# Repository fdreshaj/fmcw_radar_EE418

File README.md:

# fmcw_radar_EE418
FMCW Radar Design at 26.5 - 40 GHz

Initial Systems Level Overview
Bistatic Design

Monostatic Design

Initial Parts Search Tx bistatic:

MCU 

STM32H730VBT6

Synthesizer 
	ADF4371 62.5MHz - 32 GHz
	Refer to datasheet for more info 
	3.3V, 5V, min 200mA
	Pout = -7dBm at 30 GHz

PA  
    MAAP-118260 18-26 GHz 28.5 dB,28.5 dBm, 24 QFN
    MAAP-011319 24-30 GHz 24 dB, 27 dBm PSAT 24 QFN

Dir Coupler 
    FPC07181 20GHz ~ 40GHz 20dB 0.3dB IL, 15 dB RL

ADC

    AD4080 20 Bit 40 MSPS Differential SAR 

LNA

	PMA3-24323LN+ 24-32 GHz, fluctuates around 14.5 to 15.1 dB
	Operating Vs 4.75-5.25

TX Mixer

	ADAR2001 In 2.5-10 GHz
	2.5V analog supply, 1.8 digital supply, 4x Freq 
	Differential

RX Mixer

	ADAR2004 RF In 10-40 GHz, LO In  2.4-10.1 GHz, IF Out  0-800 MHz
	2.5V analog supply, 1.8V digital, Gain Range 21-41 dB
	Differential

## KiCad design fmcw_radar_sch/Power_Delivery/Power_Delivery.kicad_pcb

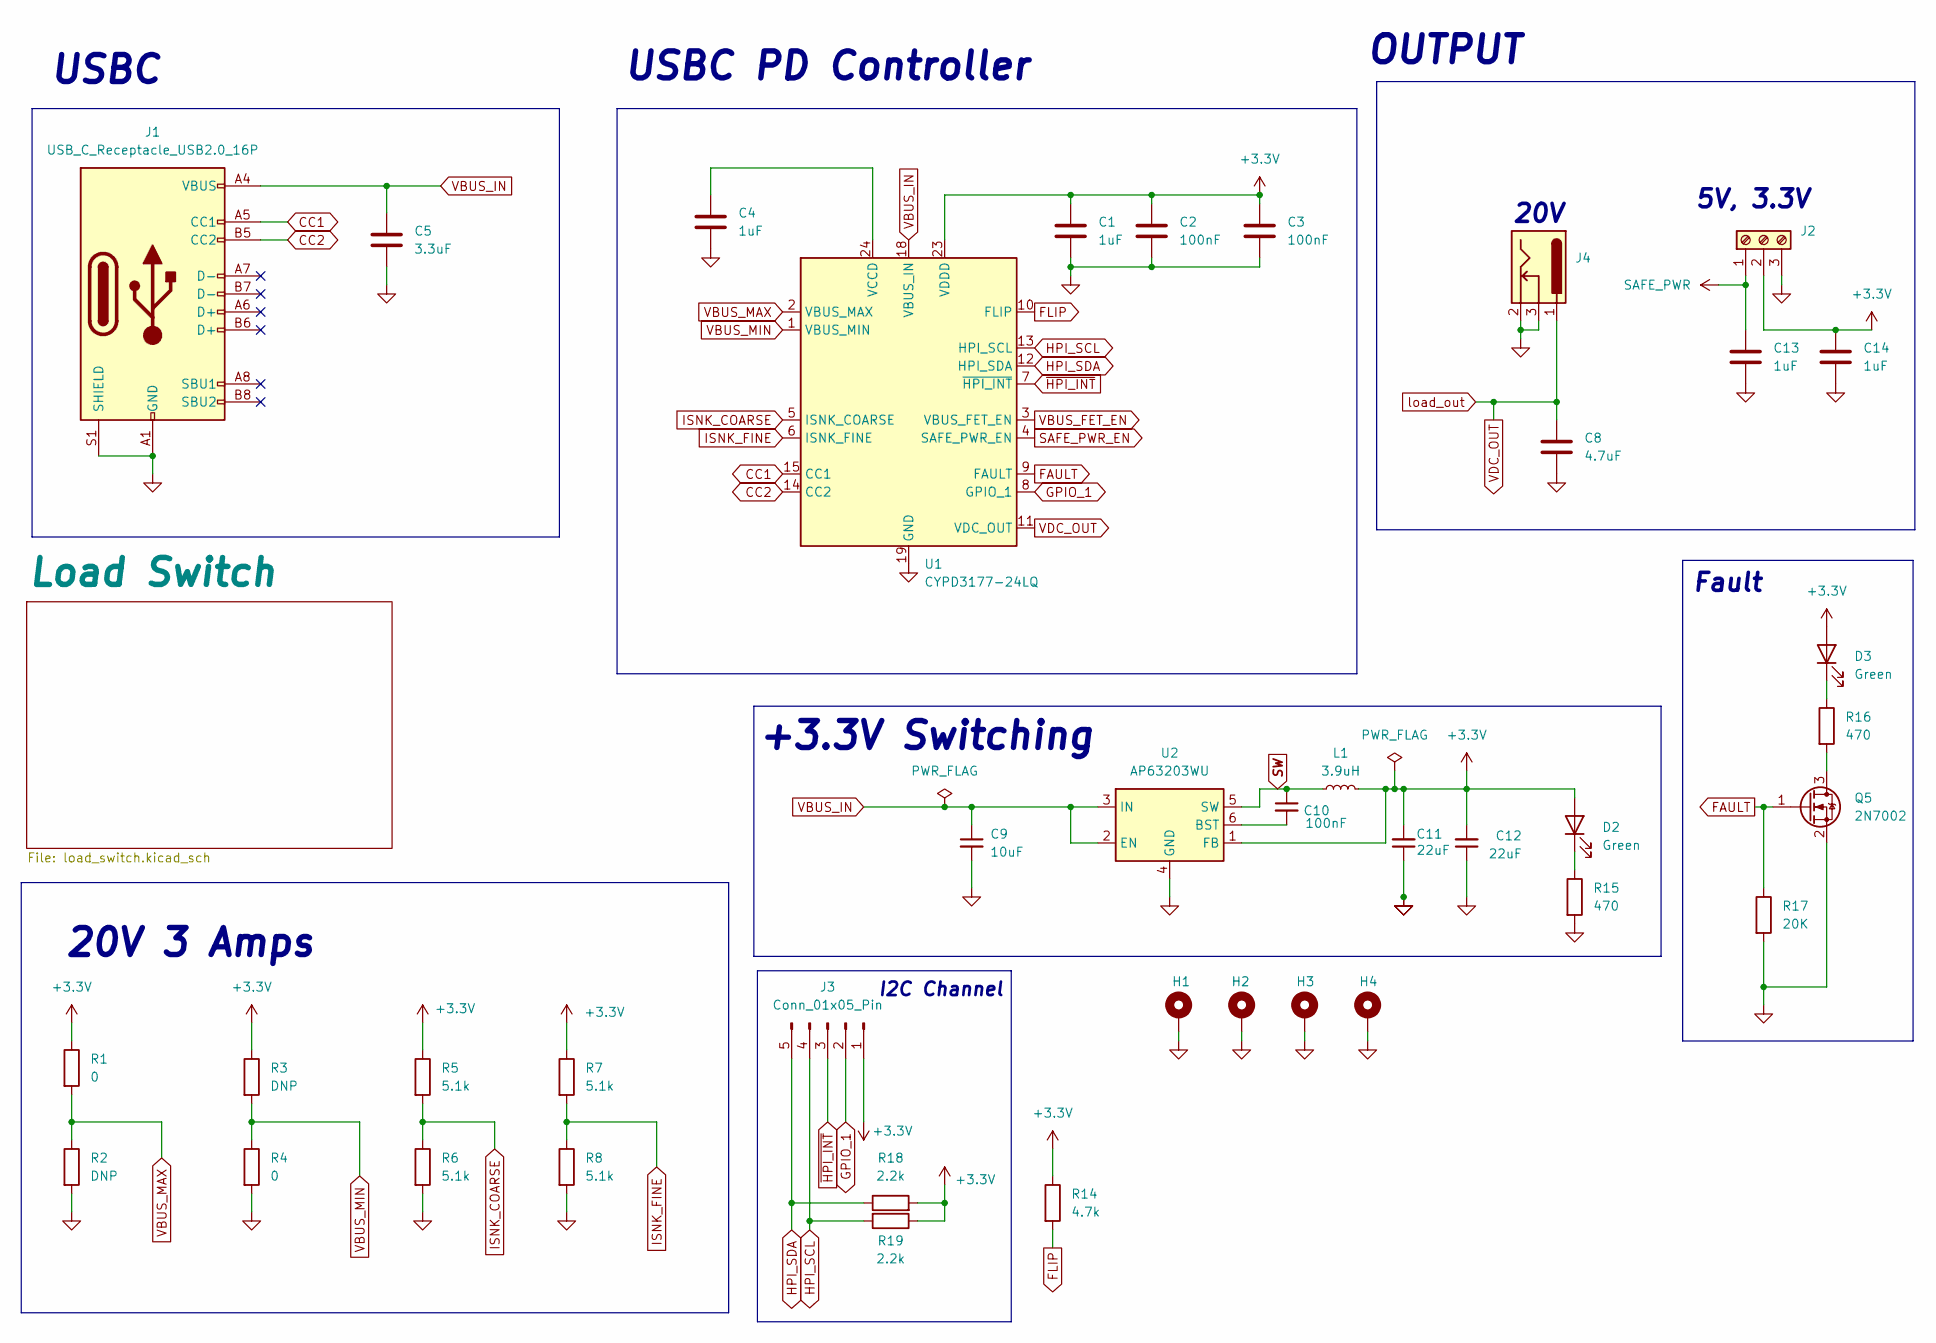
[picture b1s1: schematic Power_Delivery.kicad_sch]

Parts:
C1, C4, C13, C14: 1uF; C_0603_1608Metric
C2, C3, C10: 100nF; C_0603_1608Metric
C5: 3.3uF; C_0603_1608Metric
C8: 4.7uF; C_0603_1608Metric
C9: 10uF; C_0603_1608Metric
C11, C12: 22uF; C_1206_3216Metric
D2, D3: Green; LED_0603_1608Metric
H1, H2, H3, H4: MountingHole_Pad; MountingHole_2.5mm_Pad
J1: USB_C_Receptacle_USB2.0_16P; USB_C_Receptacle_G-Switch_GT-USB-7010ASV
J2: Screw_Terminal_01x03; TerminalBlock_Phoenix_MKDS-1,5-3-5.08_1x03_P5.08mm_Horizont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
J3: Conn_01x05_Pin; PinHeader_1x05_P2.54mm_Vertical
J4: Barrel_Jack_Switch; BarrelJack_GCT_DCJ200-10-A_Horizontal
L1: 3.9uH; L_Bourns_SDR0604
Q5: 2N7002; SOT-23
R1, R4: 0; R_0603_1608Metric
R2, R3: DNP; R_0603_1608Metric
R5, R6, R7, R8: 5.1k; R_0603_1608Metric
R14: 4.7k; R_0603_1608Metric
R15, R16: 470; R_0603_1608Metric
R17: 20K; R_0603_1608Metric
R18, R19: 2.2k; R_0603_1608Metric
U1: CYPD3177-24LQ; QFN-24-1EP_4x4mm_P0.5mm_EP2.75x2.75mm
U2: AP63203WU; TSOT-23-6

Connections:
+3.3V: C1.1, C2.1, C3.1, C11.2, C12.2, C14.2, D2.2 (A), D3.2 (A), J2.2, J3.1, L1.2, R1.1, R3.1, R5.1, R7.1, R14.1, R18.2, R19.1, U1.23 (VDDD), U2.1 (FB)
CC1: J1.A5 (CC1), U1.15 (CC1)
CC2: J1.B5 (CC2), U1.14 (CC2)
FAULT: Q5.1 (G), R17.1, U1.9 (FAULT)
FLIP: R14.2, U1.10 (FLIP)
GND: C1.2, C2.2, C3.2, C4.2, C5.2, C8.1, C9.2, C11.1, C12.1, C13.1, C14.1, H1.1, H2.1, H3.1, H4.1, J1.A1 (GND), J1.A12 (GND), J1.B1 (GND), J1.B12 (GND), J1.S1 (SHIELD), J2.3, J4.2, J4.3, Q5.2 (S), R2.2, R4.2, R6.2, R8.2, R15.2, R17.2, U1.19 (GND), U1.22 (GND), U1.25 (GND), U2.4 (GND)
GPIO_1: J3.2, U1.8 (GPIO_1)
HPI_SCL: J3.4, R19.2, U1.13 (HPI_SCL)
HPI_SDA: J3.5, R18.1, U1.12 (HPI_SDA)
ISNK_COARSE: R5.2, R6.1, U1.5 (ISNK_COARSE)
ISNK_FINE: R7.2, R8.1, U1.6 (ISNK_FINE)
unnamed: D2.1 (K), R15.1
unnamed: D3.1 (K), R16.1
unnamed: Q5.3 (D), R16.2
unnamed: C4.1, U1.24 (VCCD)
unnamed: C10.2, U2.6 (BST)
SAFE_PWR: C13.2, J2.1; also elsewhere on the board
SAFE_PWR_EN: U1.4 (SAFE_PWR_EN); also elsewhere on the board
SW: C10.1, L1.1, U2.5 (SW)
VBUS_FET_EN: U1.3 (VBUS_FET_EN); also elsewhere on the board
VBUS_IN: C5.1, C9.1, J1.A4 (VBUS), J1.A9 (VBUS), J1.B4 (VBUS), J1.B9 (VBUS), U1.18 (VBUS_IN), U2.2 (EN), U2.3 (IN); also elsewhere on the board
VBUS_MAX: R1.2, R2.1, U1.2 (VBUS_MAX)
VBUS_MIN: R3.2, R4.1, U1.1 (VBUS_MIN)
VDC_OUT: C8.2, J4.1, U1.11 (VDC_OUT); also elsewhere on the board
~HPI_INT: J3.3, U1.7 (~HPI_INT)

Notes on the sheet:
5V, 3.3V
USBC
20V
Fault
I2C Channel
OUTPUT
USBC PD Controller
20V 3 Amps
+3.3V Switching

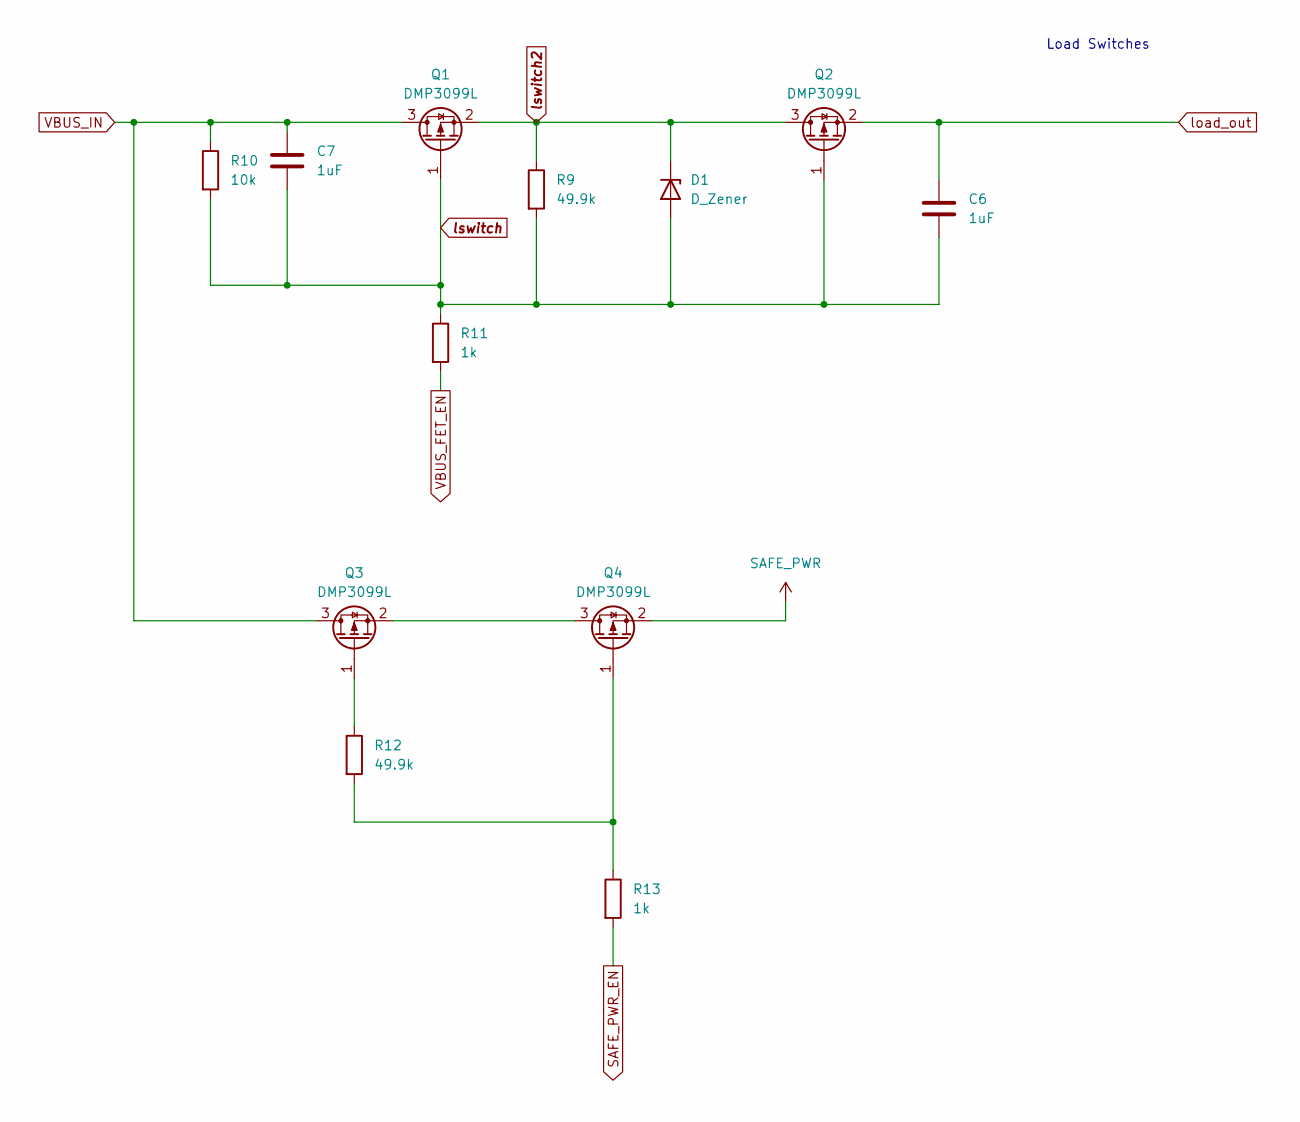
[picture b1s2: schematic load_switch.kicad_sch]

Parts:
C6, C7: 1uF; C_0603_1608Metric
D1: D_Zener; D_0603_1608Metric
Q1, Q2, Q3, Q4: DMP3099L; SOT-23
R9, R12: 49.9k; R_0603_1608Metric
R10: 10k; R_0603_1608Metric
R11, R13: 1k; R_0603_1608Metric

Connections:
unnamed: Q3.1 (G), R12.1
unnamed: Q3.2 (S), Q4.3 (D)
unnamed: Q4.1 (G), R12.2, R13.1
SAFE_PWR: Q4.2 (S); also elsewhere on the board
SAFE_PWR_EN: R13.2; also elsewhere on the board
VBUS_FET_EN: R11.2; also elsewhere on the board
VBUS_IN: C7.1, Q1.3 (D), Q3.3 (D), R10.1; also elsewhere on the board
VDC_OUT: C6.1, Q2.2 (S); also elsewhere on the board
lswitch: C6.2, C7.2, D1.2 (A), Q1.1 (G), Q2.1 (G), R9.2, R10.2, R11.1
lswitch2: D1.1 (K), Q1.2 (S), Q2.3 (D), R9.1

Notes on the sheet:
Load Switches

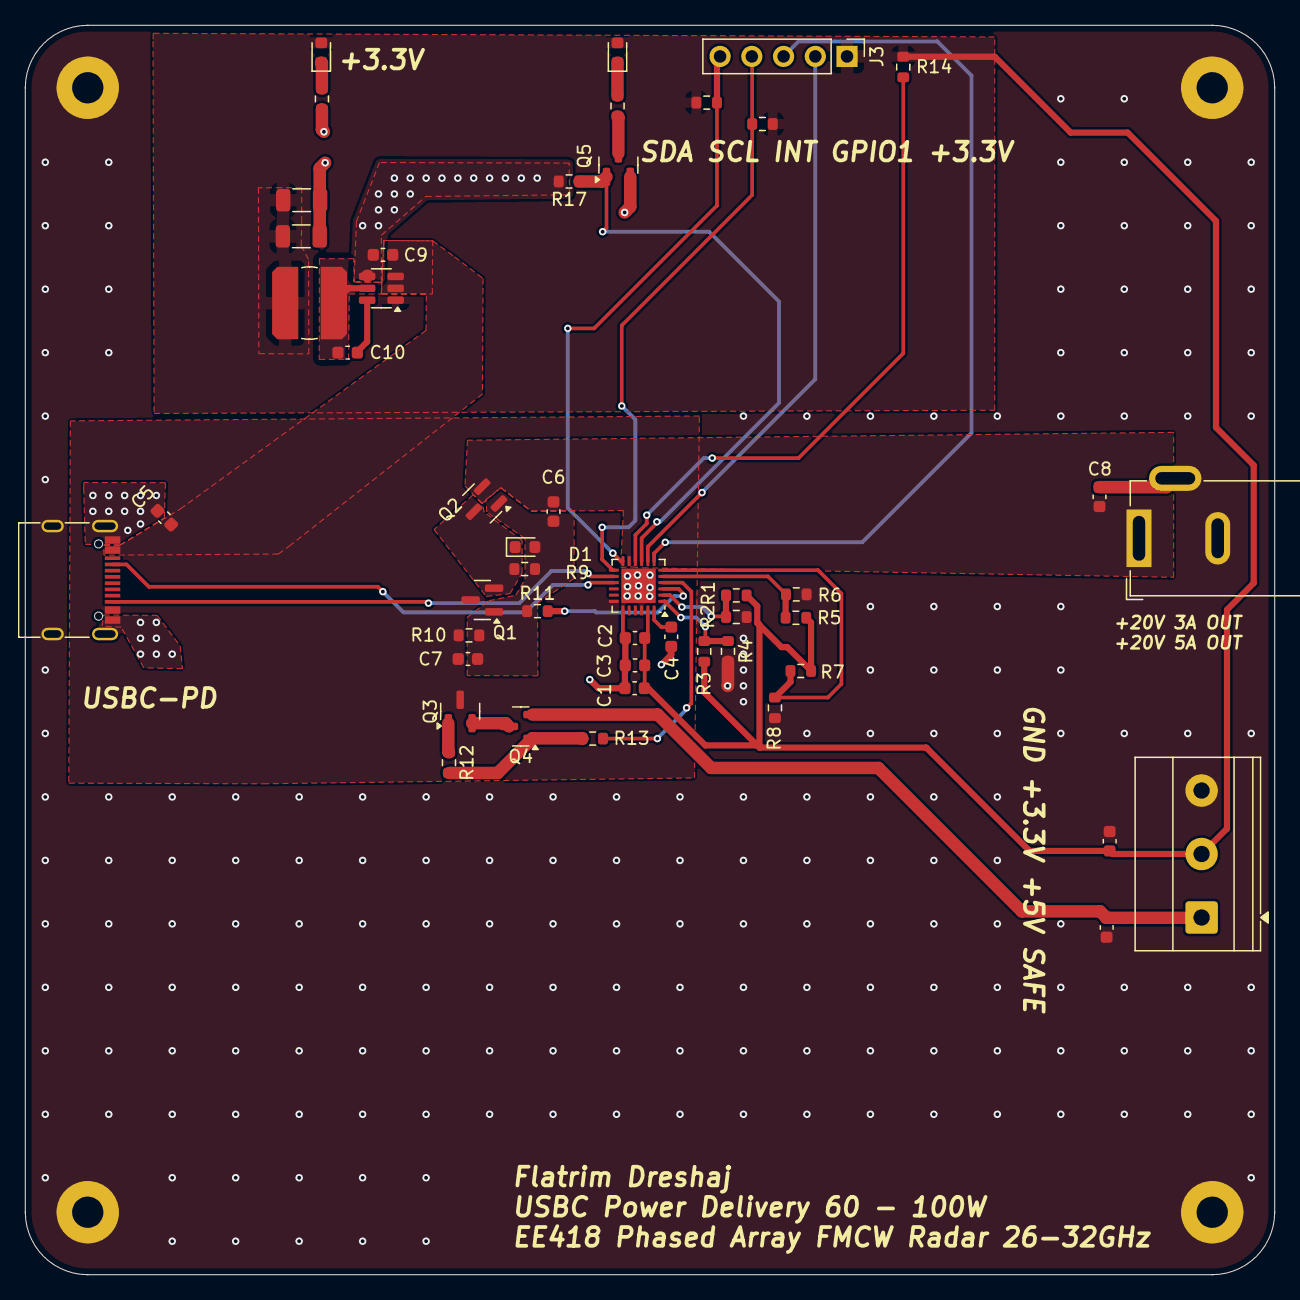
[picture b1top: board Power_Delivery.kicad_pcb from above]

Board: 2 copper layers, 100.0 x 100.0 mm, 52 parts (0 on the bottom side), 30 nets.

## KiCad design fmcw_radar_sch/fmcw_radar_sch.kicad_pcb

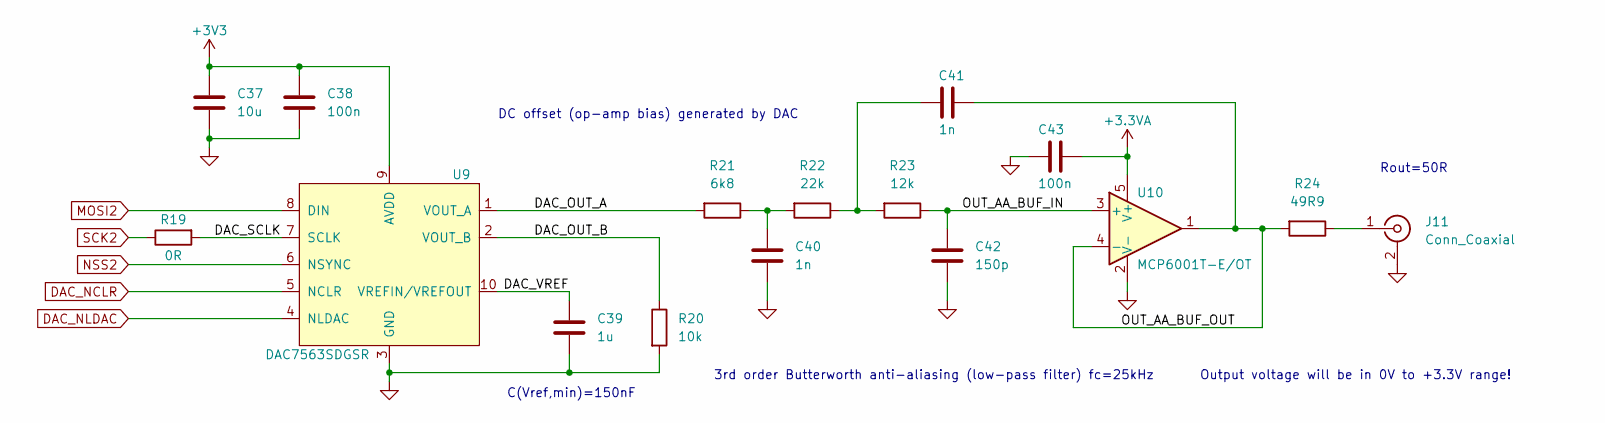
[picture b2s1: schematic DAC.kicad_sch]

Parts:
C37: 10u; C_0603_1608Metric
C38, C43: 100n; C_0402_1005Metric
C39: 1u; C_0603_1608Metric
C40, C41: 1n; C_0402_1005Metric
C42: 150p; C_0402_1005Metric
J11: Conn_Coaxial; BNC_Amphenol_031-5539_Vertical
R19: 0R; R_0402_1005Metric
R20: 10k; R_0402_1005Metric
R21: 6k8; R_0402_1005Metric
R22: 22k; R_0402_1005Metric
R23: 12k; R_0402_1005Metric
R24: 49R9; R_0402_1005Metric
U9: DAC7563SDGSR; DGS0010A_L
U10: MCP6001T-E/OT; SOT-23-5

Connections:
+3.3VA: C43.1, U10.5 (V+); also elsewhere on the board
+3V3: C37.1, C38.1, U9.9 (AVDD)
/DAC/DAC_OUT_A: R21.2, U9.1 (VOUT_A)
/DAC/DAC_OUT_B: R20.1, U9.2 (VOUT_B)
/DAC/DAC_SCLK: R19.2, U9.7 (SCLK)
/DAC/DAC_VREF: C39.1, U9.10 (VREFIN/VREFOUT)
/DAC/OUT_AA_BUF_IN: C42.1, R23.1, U10.3 (+)
/DAC/OUT_AA_BUF_OUT: C41.2, R24.2, U10.1, U10.4 (-)
DAC_NCLR: U9.5 (NCLR); also elsewhere on the board
DAC_NLDAC: U9.4 (NLDAC); also elsewhere on the board
GND: C37.2, C38.2, C39.2, C40.2, C42.2, C43.2, J11.2 (Ext), R20.2, U9.3 (GND), U10.2 (V-); also elsewhere on the board
MOSI2: U9.8 (DIN); also elsewhere on the board
NSS2: U9.6 (NSYNC); also elsewhere on the board
unnamed: C40.1, R21.1, R22.2
unnamed: C41.1, R22.1, R23.2
unnamed: J11.1 (In), R24.1
SCK2: R19.1; also elsewhere on the board

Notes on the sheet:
DC offset (op-amp bias) generated by DAC
3rd order Butterworth anti-aliasing (low-pass filter) fc=25kHz
Rout=50R
C(Vref,min)=150nF
Output voltage will be in 0V to +3.3V range!

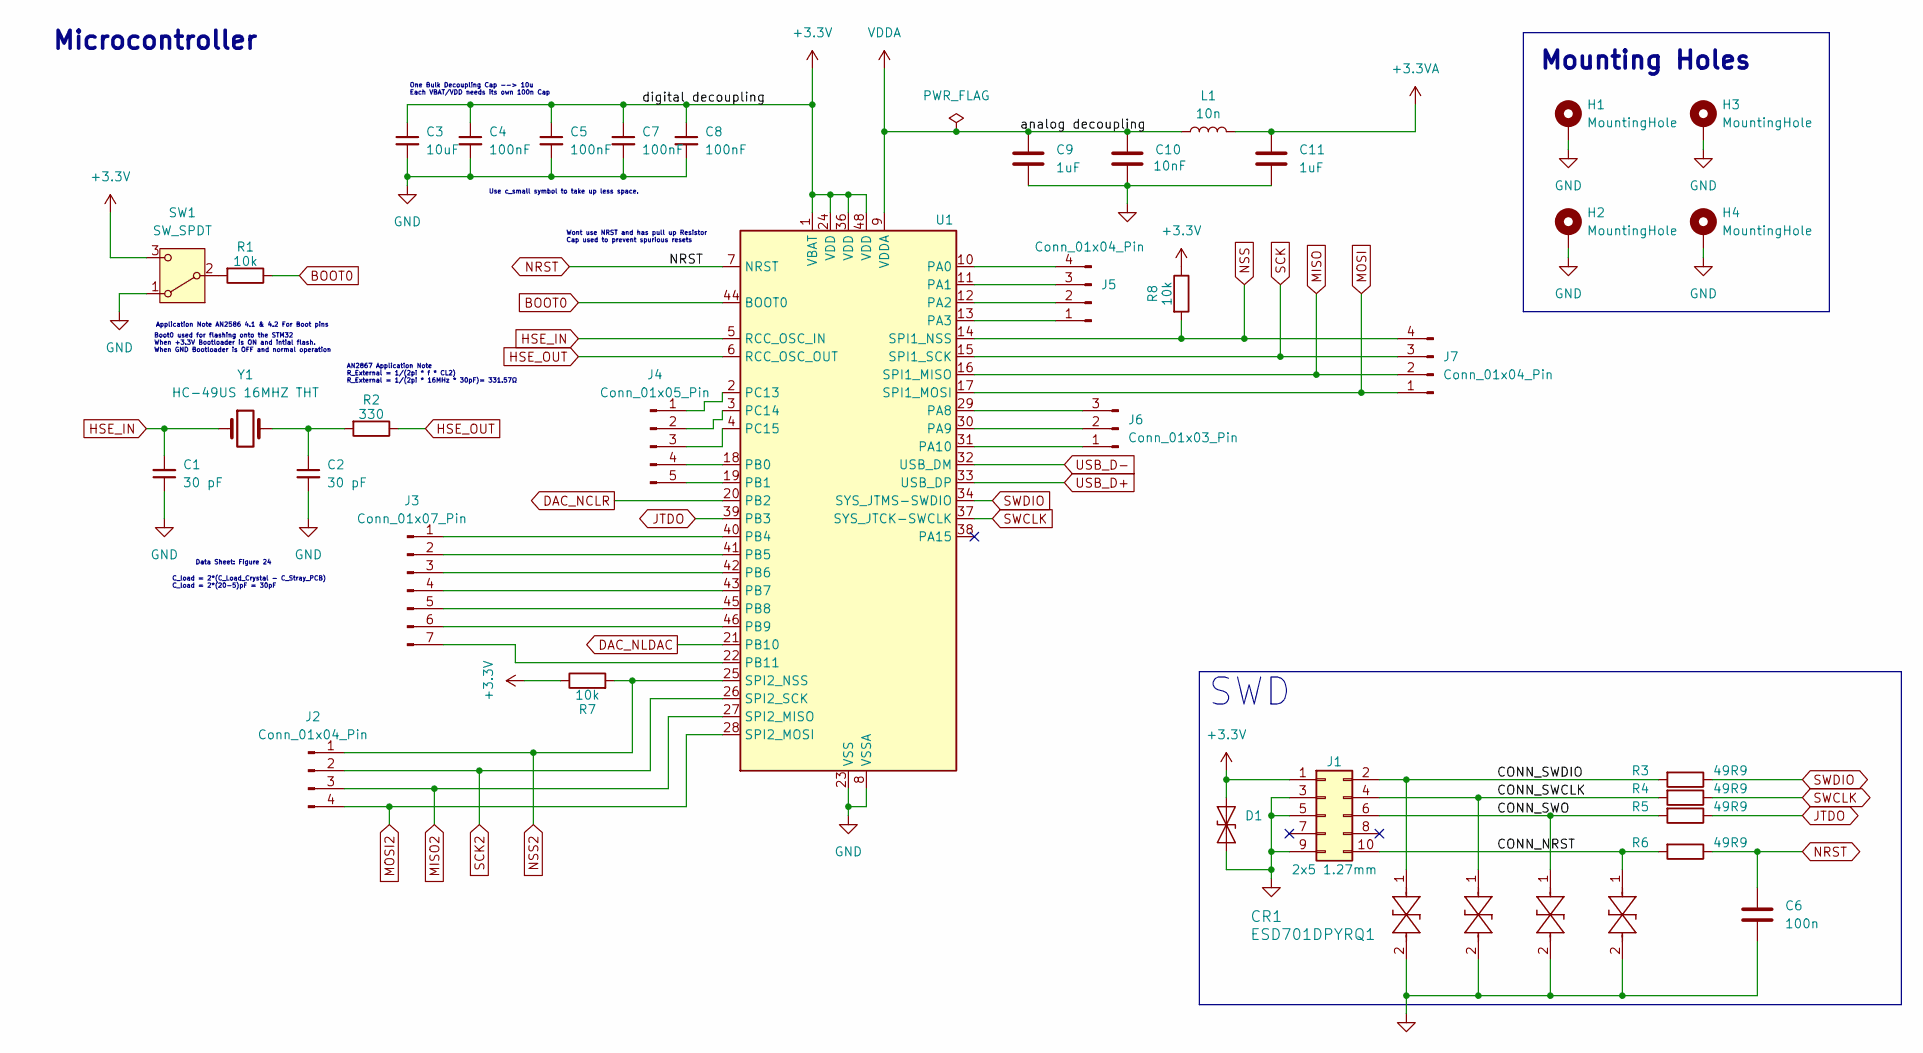
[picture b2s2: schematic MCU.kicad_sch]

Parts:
C1, C2: 30 pF; C_1206_3216Metric_Pad1.33x1.80mm_HandSolder
C3: 10uF; C_1206_3216Metric_Pad1.33x1.80mm_HandSolder
C4, C5, C7, C8: 100nF; C_1206_3216Metric_Pad1.33x1.80mm_HandSolder
C6: 100n; C_0603_1608Metric_Pad1.08x0.95mm_HandSolder
C9, C11: 1uF; C_0603_1608Metric_Pad1.08x0.95mm_HandSolder
C10: 10nF; C_0603_1608Metric_Pad1.08x0.95mm_HandSolder
CR1, CR2, CR3, CR4: ESD701DPYRQ1; X1SON2_DPY_TEX
D1: ESD131-B1-W0201; Nexperia_DSN0603-2_0.6x0.3mm_P0.4mm
H1, H2, H3, H4: MountingHole; MountingHole_3.2mm_M3_Pad
J1: 2x5 1.27mm; PinHeader_2x05_P2.54mm_Vertical
J2, J5, J7: Conn_01x04_Pin; PinHeader_1x04_P2.54mm_Vertical
J3: Conn_01x07_Pin; PinHeader_1x07_P2.54mm_Vertical
J4: Conn_01x05_Pin; PinHeader_1x05_P2.54mm_Vertical
J6: Conn_01x03_Pin; PinHeader_1x03_P2.54mm_Vertical
L1: 10n; L_1206_3216Metric
R1, R7, R8: 10k; R_1206_3216Metric_Pad1.30x1.75mm_HandSolder
R2: 330; R_1206_3216Metric_Pad1.30x1.75mm_HandSolder
R3, R4, R5, R6: 49R9; R_0603_1608Metric_Pad0.98x0.95mm_HandSolder
SW1: SW_SPDT; SW_Slide_SPDT_Straight_CK_OS102011MS2Q
U1: STM32F103C8T6; LQFP-48_7x7mm_P0.5mm
Y1: HC-49US 16MHZ THT; Crystal_HC49-4H_Vertical

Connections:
+3.3V: C3.1, C4.1, C5.1, C7.1, C8.1, D1.2 (A2), J1.1, R7.1, R8.1, SW1.3 (C), U1.1 (VBAT), U1.24 (VDD), U1.36 (VDD), U1.48 (VDD); also elsewhere on the board
+3.3VA: C11.1, L1.2; also elsewhere on the board
/MCU/CONN_NRST: CR4.1, J1.10, R6.2
/MCU/CONN_SWCLK: CR2.1, J1.4, R4.2
/MCU/CONN_SWDIO: CR1.1, J1.2, R3.2
/MCU/CONN_SWO: CR3.1, J1.6, R5.2
BOOT0: R1.1, U1.44 (BOOT0)
DAC_NCLR: U1.20 (PB2); also elsewhere on the board
DAC_NLDAC: U1.21 (PB10); also elsewhere on the board
GND: C1.1, C2.2, C3.2, C4.2, C5.2, C6.2, C7.2, C8.2, C9.2, C10.2, C11.2, CR1.2, CR2.2, CR3.2, CR4.2, D1.1 (A1), H1.1, H2.1, H3.1, H4.1, J1.3, J1.5, J1.9, SW1.1 (A), U1.8 (VSSA), U1.23 (VSS), U1.35 (VSS), U1.47 (VSS); also elsewhere on the board
HSE_IN: C1.2, U1.5 (RCC_OSC_IN), Y1.1
HSE_OUT: R2.1, U1.6 (RCC_OSC_OUT)
JTDO: R5.1, U1.39 (PB3)
MISO: J7.2, U1.16 (SPI1_MISO)
MISO2: J2.3, U1.27 (SPI2_MISO)
MOSI: J7.1, U1.17 (SPI1_MOSI)
MOSI2: J2.4, U1.28 (SPI2_MOSI); also elsewhere on the board
NRST: C6.1, R6.1, U1.7 (NRST)
NSS: J7.4, R8.2, U1.14 (SPI1_NSS)
NSS2: J2.1, R7.2, U1.25 (SPI2_NSS); also elsewhere on the board
unnamed: C2.1, R2.2, Y1.2
unnamed: J3.1, U1.40 (PB4)
unnamed: J3.2, U1.41 (PB5)
unnamed: J3.3, U1.42 (PB6)
unnamed: J3.4, U1.43 (PB7)
unnamed: J3.5, U1.45 (PB8)
unnamed: J3.6, U1.46 (PB9)
unnamed: J3.7, U1.22 (PB11)
unnamed: J4.1, U1.2 (PC13)
unnamed: J4.2, U1.3 (PC14)
unnamed: J4.3, U1.4 (PC15)
unnamed: J4.4, U1.18 (PB0)
unnamed: J4.5, U1.19 (PB1)
unnamed: J5.1, U1.13 (PA3)
unnamed: J5.2, U1.12 (PA2)
unnamed: J5.3, U1.11 (PA1)
unnamed: J5.4, U1.10 (PA0)
unnamed: J6.1, U1.31 (PA10)
unnamed: J6.2, U1.30 (PA9)
unnamed: J6.3, U1.29 (PA8)
unnamed: R1.2, SW1.2 (B)
SCK: J7.3, U1.15 (SPI1_SCK)
SCK2: J2.2, U1.26 (SPI2_SCK); also elsewhere on the board
SWCLK: R4.1, U1.37 (SYS_JTCK-SWCLK)
SWDIO: R3.1, U1.34 (SYS_JTMS-SWDIO)
USB_D+: U1.33 (USB_DP); also elsewhere on the board
USB_D-: U1.32 (USB_DM); also elsewhere on the board
VDDA: C9.1, C10.1, L1.1, U1.9 (VDDA)

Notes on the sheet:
Application Note AN2586 4.1 & 4.2 For Boot pins
Wont use NRST and has pull up Resistor Cap used to prevent spurious resets
Use c_small symbol to take up less space.
SWD
C_load = 2*(C_Load_Crystal - C_Stray_PCB) C_load = 2*(20-5)pF = 30pF
Mounting Holes
Microcontroller
One Bulk Decoupling Cap --> 10u Each VBAT/VDD needs its own 100n Cap
Data Sheet: Figure 24
Boot0 used for flashing onto the STM32 When +3.3V Bootloader is ON and intial flash. When GND Bootloader is OFF and normal operation
AN2867 Application Note R_External = 1/(2pi * f * CL2) R_External = 1/(2pi * 16MHz * 30pF)= 331.57Ω

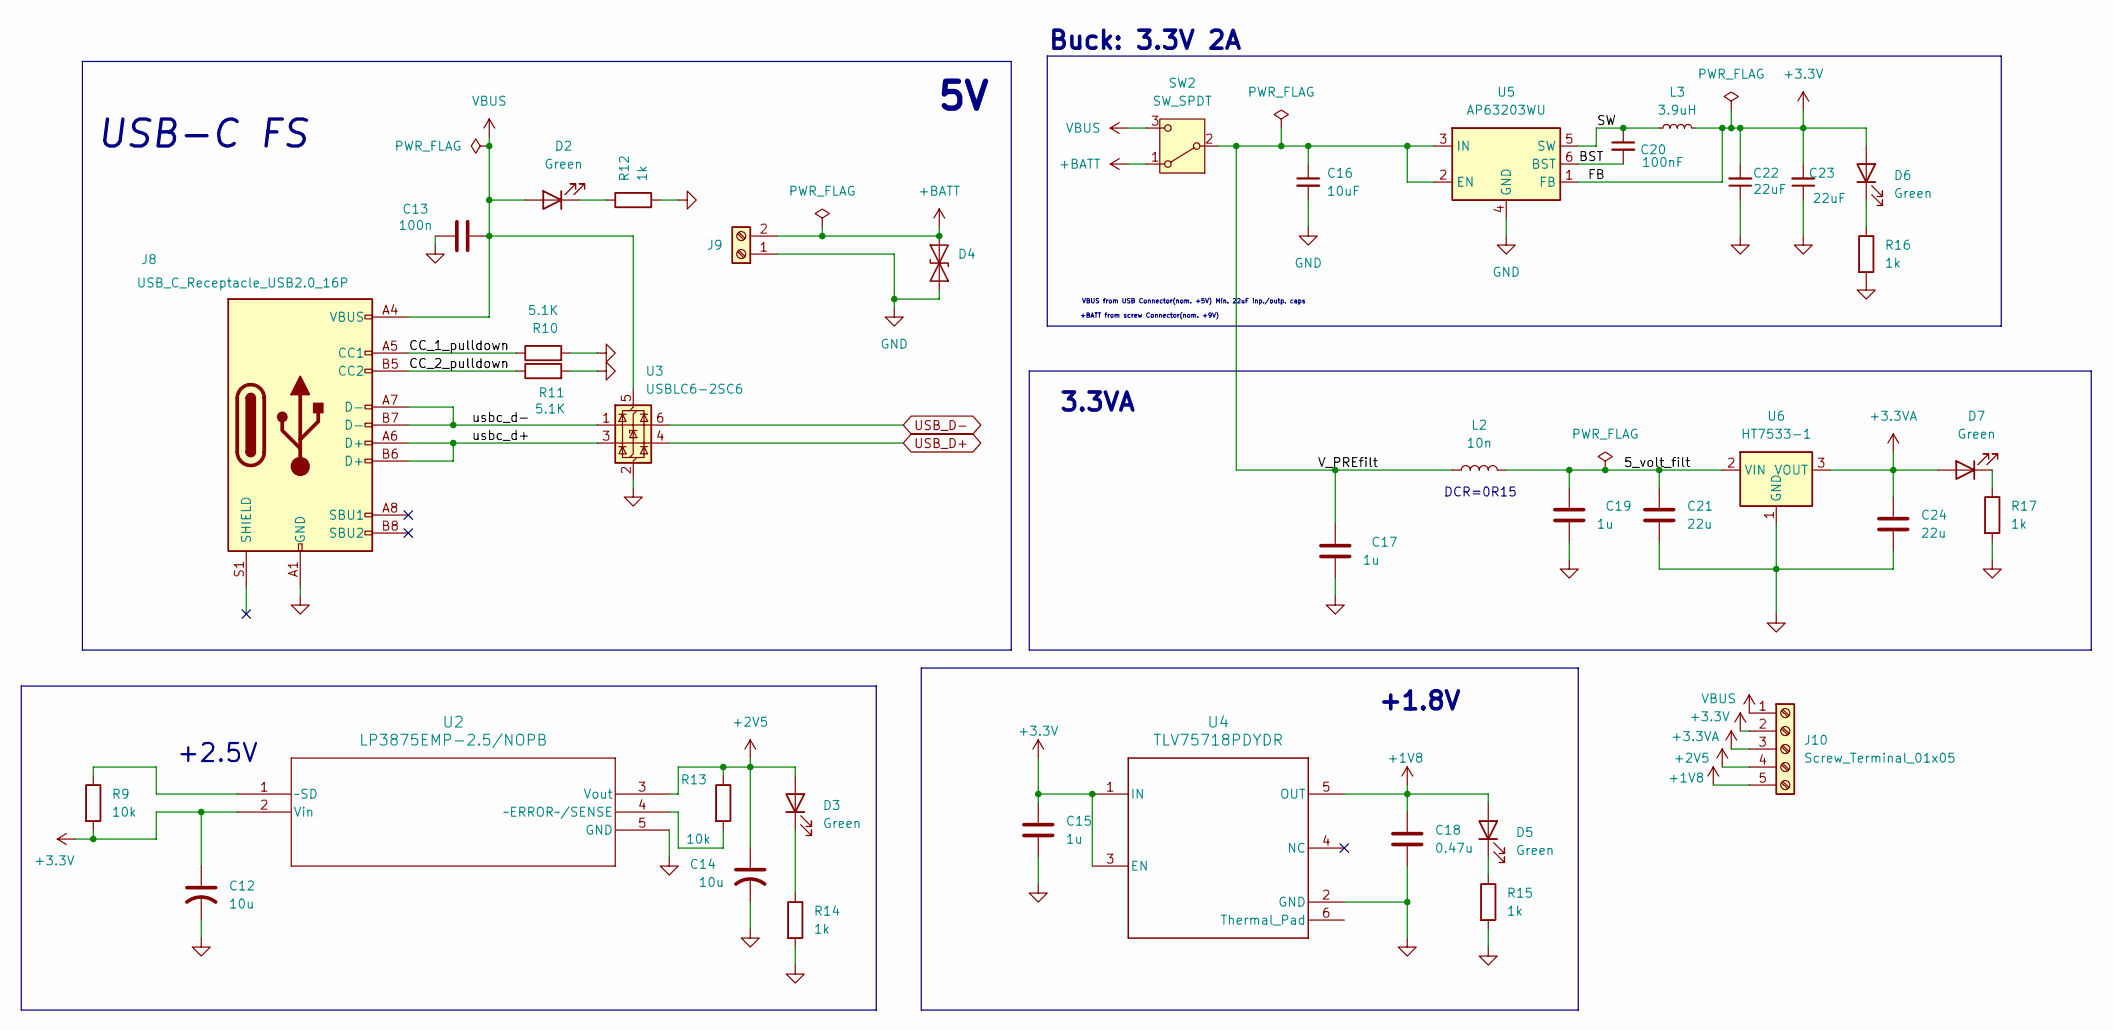
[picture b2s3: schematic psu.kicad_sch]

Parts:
C12, C14: 10u; C_1206_3216Metric_Pad1.33x1.80mm_HandSolder
C13: 100n; C_0603_1608Metric
C15: 1u; C_1206_3216Metric_Pad1.33x1.80mm_HandSolder
C16: 10uF; C_1206_3216Metric_Pad1.33x1.80mm_HandSolder
C17, C19: 1u; C_0805_2012Metric
C18: 0.47u; C_1206_3216Metric_Pad1.33x1.80mm_HandSolder
C20: 100nF; C_1206_3216Metric_Pad1.33x1.80mm_HandSolder
C21, C24: 22u; C_0805_2012Metric
C22, C23: 22uF; C_1206_3216Metric_Pad1.33x1.80mm_HandSolder
D2, D3, D5, D6, D7: Green; LED_0603_1608Metric_Pad1.05x0.95mm_HandSolder
D4: ESD131-B1-W0201; Infineon_SG-WLL-2-3_0.58x0.28_P0.36mm
J8: USB_C_Receptacle_USB2.0_16P; USB_C_Receptacle_G-Switch_GT-USB-7010ASV
J9: Screw_Terminal_01x02; TerminalBlock_MaiXu_MX126-5.0-02P_1x02_P5.00mm
J10: Screw_Terminal_01x05; TerminalBlock_Phoenix_MKDS-3-5-5.08_1x05_P5.08mm_Horizontal
L2: 10n; L_APV_ANR6020
L3: 3.9uH; L_Bourns_SDR0604
R9, R13: 10k; R_1206_3216Metric_Pad1.30x1.75mm_HandSolder
R10, R11: 5.1K; R_0603_1608Metric_Pad0.98x0.95mm_HandSolder
R12, R14, R15, R16, R17: 1k; R_0603_1608Metric_Pad0.98x0.95mm_HandSolder
SW2: SW_SPDT; SW_Slide_SPDT_Straight_CK_OS102011MS2Q
U2: LP3875EMP-2.5/NOPB; MP05A
U3: USBLC6-2SC6; SOT-23-6_Handsoldering
U4: TLV75718PDYDR; DYD0005A-MFG
U5: AP63203WU; TSOT-23-6
U6: HT7533-1; SOT-89-3_Handsoldering

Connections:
+1V8: C18.1, D5.2 (A), J10.5, U4.5 (OUT)
+2V5: C14.1, D3.2 (A), J10.4, R13.1, U2.3 (Vout)
+3.3V: C12.1, C15.1, C22.2, C23.2, D6.2 (A), J10.2, L3.2, R9.2, U2.2 (Vin), U4.1 (IN), U4.3 (EN), U5.1 (FB); also elsewhere on the board
+3.3VA: C24.1, D7.2 (A), J10.3, U6.3 (VOUT); also elsewhere on the board
+BATT: D4.2 (A2), J9.2, SW2.1 (A)
/Power System/5_volt_filt: C19.1, C21.1, L2.2, U6.2 (VIN)
/Power System/BST: C20.2, U5.6 (BST)
/Power System/CC_1_pulldown: J8.A5 (CC1), R10.1
/Power System/CC_2_pulldown: J8.B5 (CC2), R11.1
/Power System/SW: C20.1, L3.1, U5.5 (SW)
/Power System/V_PREfilt: C16.1, C17.1, L2.1, SW2.2 (B), U5.2 (EN), U5.3 (IN)
/Power System/usbc_d+: J8.A6 (D+), J8.B6 (D+), U3.3 (I/O2)
/Power System/usbc_d-: J8.A7 (D-), J8.B7 (D-), U3.1 (I/O1)
GND: C12.2, C13.1, C14.2, C15.2, C16.2, C17.2, C18.2, C19.2, C21.2, C22.1, C23.1, C24.2, D4.1 (A1), J8.A1 (GND), J8.A12 (GND), J8.B1 (GND), J8.B12 (GND), J9.1, R10.2, R11.2, R12.2, R14.2, R15.2, R16.2, R17.2, U2.5 (GND), U3.2 (GND), U4.2 (GND), U5.4 (GND), U6.1 (GND); also elsewhere on the board
unnamed: D2.1 (K), R12.1
unnamed: D3.1 (K), R14.1
unnamed: D5.1 (K), R15.1
unnamed: D6.1 (K), R16.1
unnamed: D7.1 (K), R17.1
unnamed: R13.2, U2.4 (~ERROR~/SENSE)
unnamed: R9.1, U2.1 (~SD)
USB_D+: U3.4 (I/O2); also elsewhere on the board
USB_D-: U3.6 (I/O1); also elsewhere on the board
VBUS: C13.2, D2.2 (A), J8.A4 (VBUS), J8.A9 (VBUS), J8.B4 (VBUS), J8.B9 (VBUS), J10.1, SW2.3 (C), U3.5 (VBUS)

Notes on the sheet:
+1.8V
+BATT from screw Connector(nom. +9V)
Buck: 3.3V 2A
DCR=0R15
+2.5V
VBUS from USB Connector(nom. +5V) Min. 22uF inp./outp. caps
3.3VA
USB-C FS

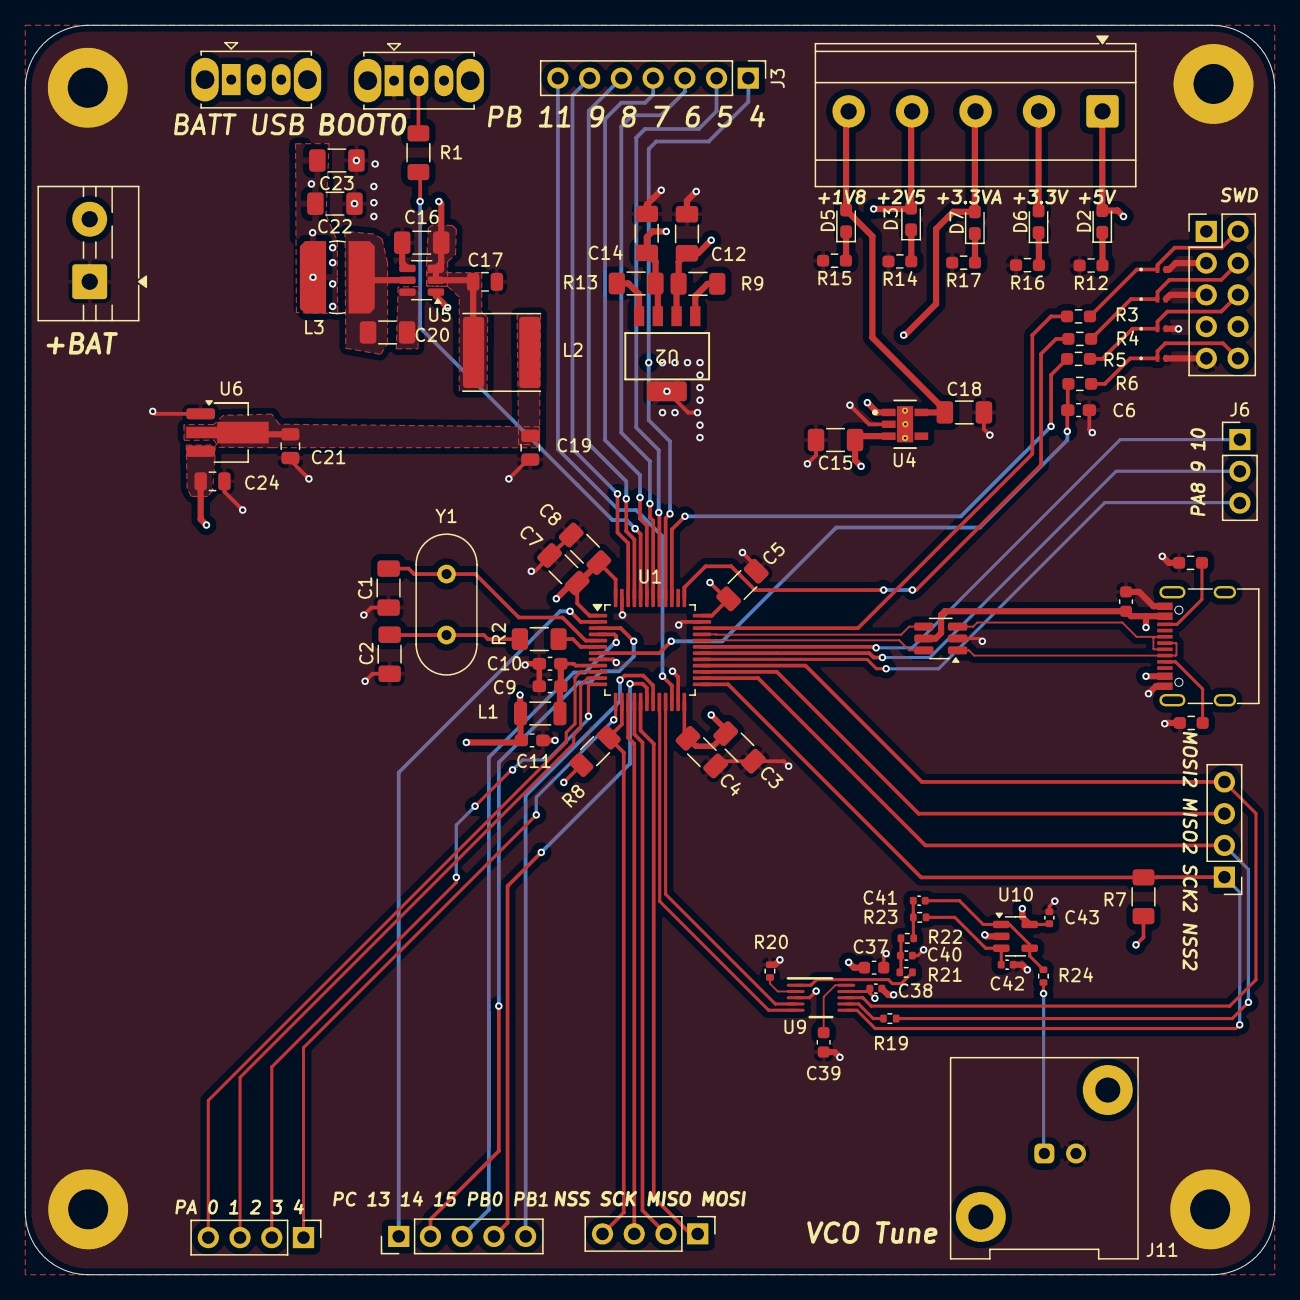
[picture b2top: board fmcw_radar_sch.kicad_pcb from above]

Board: 4 copper layers, 100.0 x 100.0 mm, 92 parts (0 on the bottom side), 77 nets.

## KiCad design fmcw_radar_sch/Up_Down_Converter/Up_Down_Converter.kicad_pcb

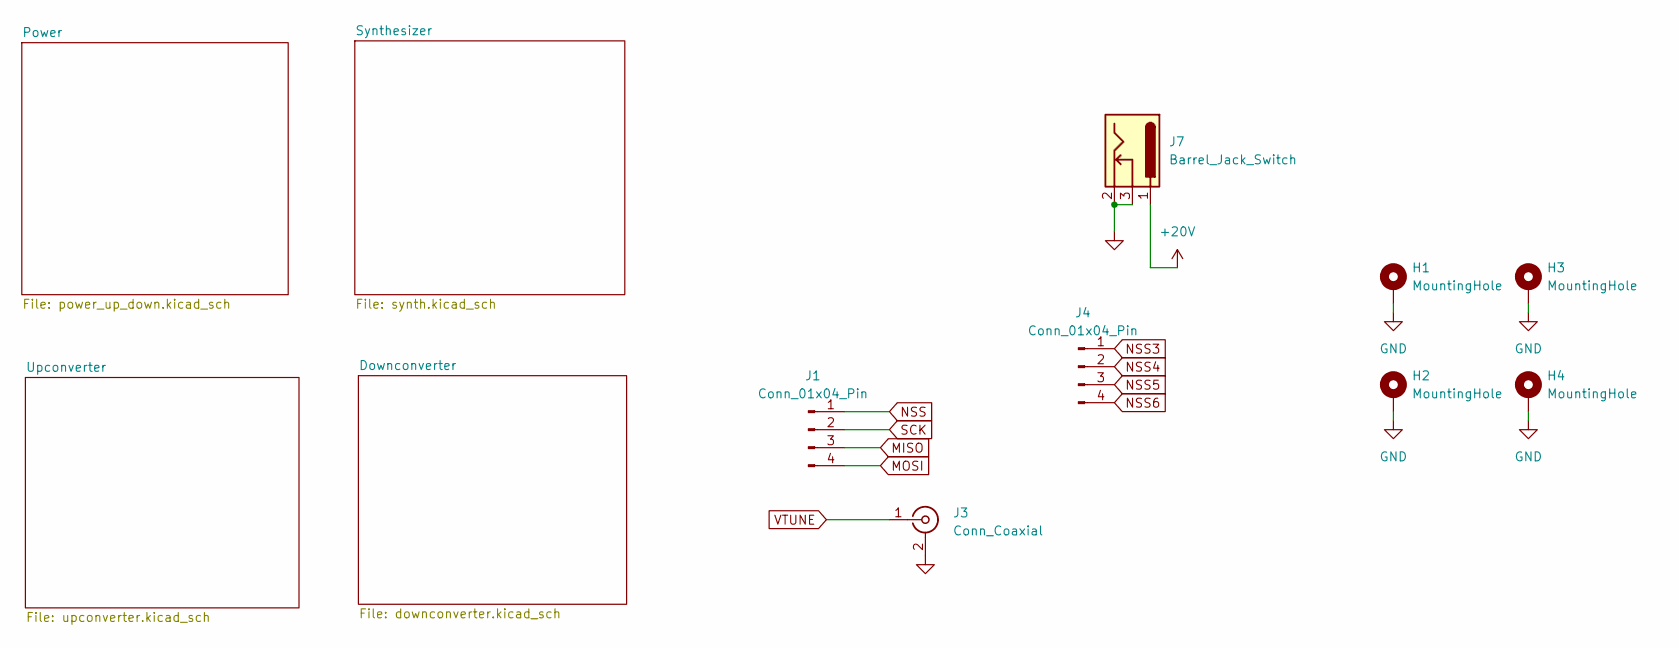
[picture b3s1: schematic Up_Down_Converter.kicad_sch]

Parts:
H1, H2, H3, H4: MountingHole; MountingHole_3.2mm_M3_Pad
J1, J4: Conn_01x04_Pin; PinHeader_1x04_P2.54mm_Vertical
J3: Conn_Coaxial; SMA_Amphenol_132134-10_Vertical
J7: Barrel_Jack_Switch; BarrelJack_Horizontal

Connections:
+20V: J7.1; also elsewhere on the board
GND: H1.1, H2.1, H3.1, H4.1, J3.2 (Ext), J7.2, J7.3; also elsewhere on the board
MISO: J1.3; also elsewhere on the board
MOSI: J1.4; also elsewhere on the board
NSS: J1.1; also elsewhere on the board
NSS3: J4.1; also elsewhere on the board
NSS4: J4.2; also elsewhere on the board
NSS5: J4.3
NSS6: J4.4
SCK: J1.2; also elsewhere on the board
VTUNE: J3.1 (In); also elsewhere on the board
